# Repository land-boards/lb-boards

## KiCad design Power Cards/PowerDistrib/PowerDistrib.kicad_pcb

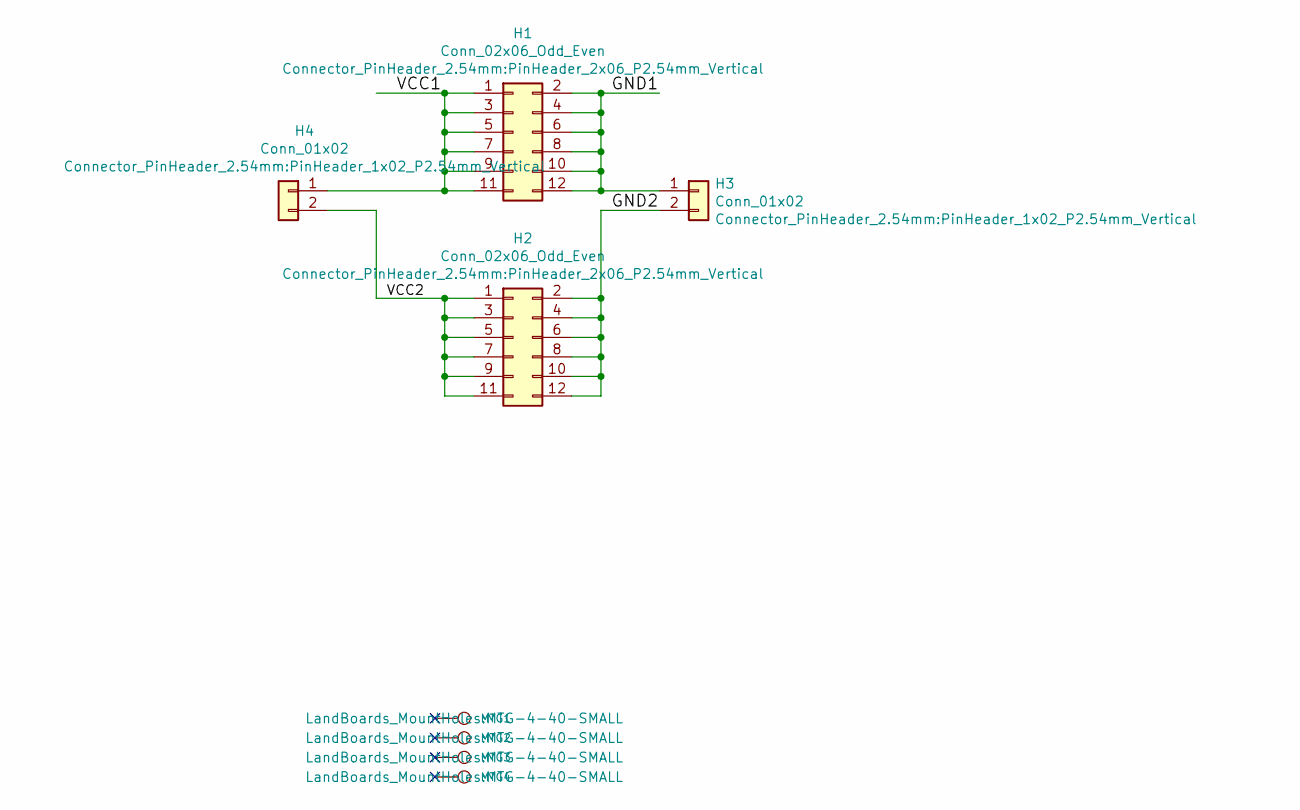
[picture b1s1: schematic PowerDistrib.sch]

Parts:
H1, H2: Conn_02x06_Odd_Even; PinHeader_2x06_P2.54mm_Vertical
H3, H4: Conn_01x02; PinHeader_1x02_P2.54mm_Vertical
MTG1, MTG2, MTG3, MTG4: CONN_1; MTG-4-40-SMALL

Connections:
/GND1: H1.2, H1.4, H1.6, H1.8, H1.10, H1.12, H3.1
/GND2: H2.2, H2.4, H2.6, H2.8, H2.10, H2.12, H3.2
/VCC1: H1.1, H1.3, H1.5, H1.7, H1.9, H1.11, H4.1
/VCC2: H2.1, H2.3, H2.5, H2.7, H2.9, H2.11, H4.2

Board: 2 copper layers, 8 parts (0 on the bottom side), 4 nets, no tracks yet.

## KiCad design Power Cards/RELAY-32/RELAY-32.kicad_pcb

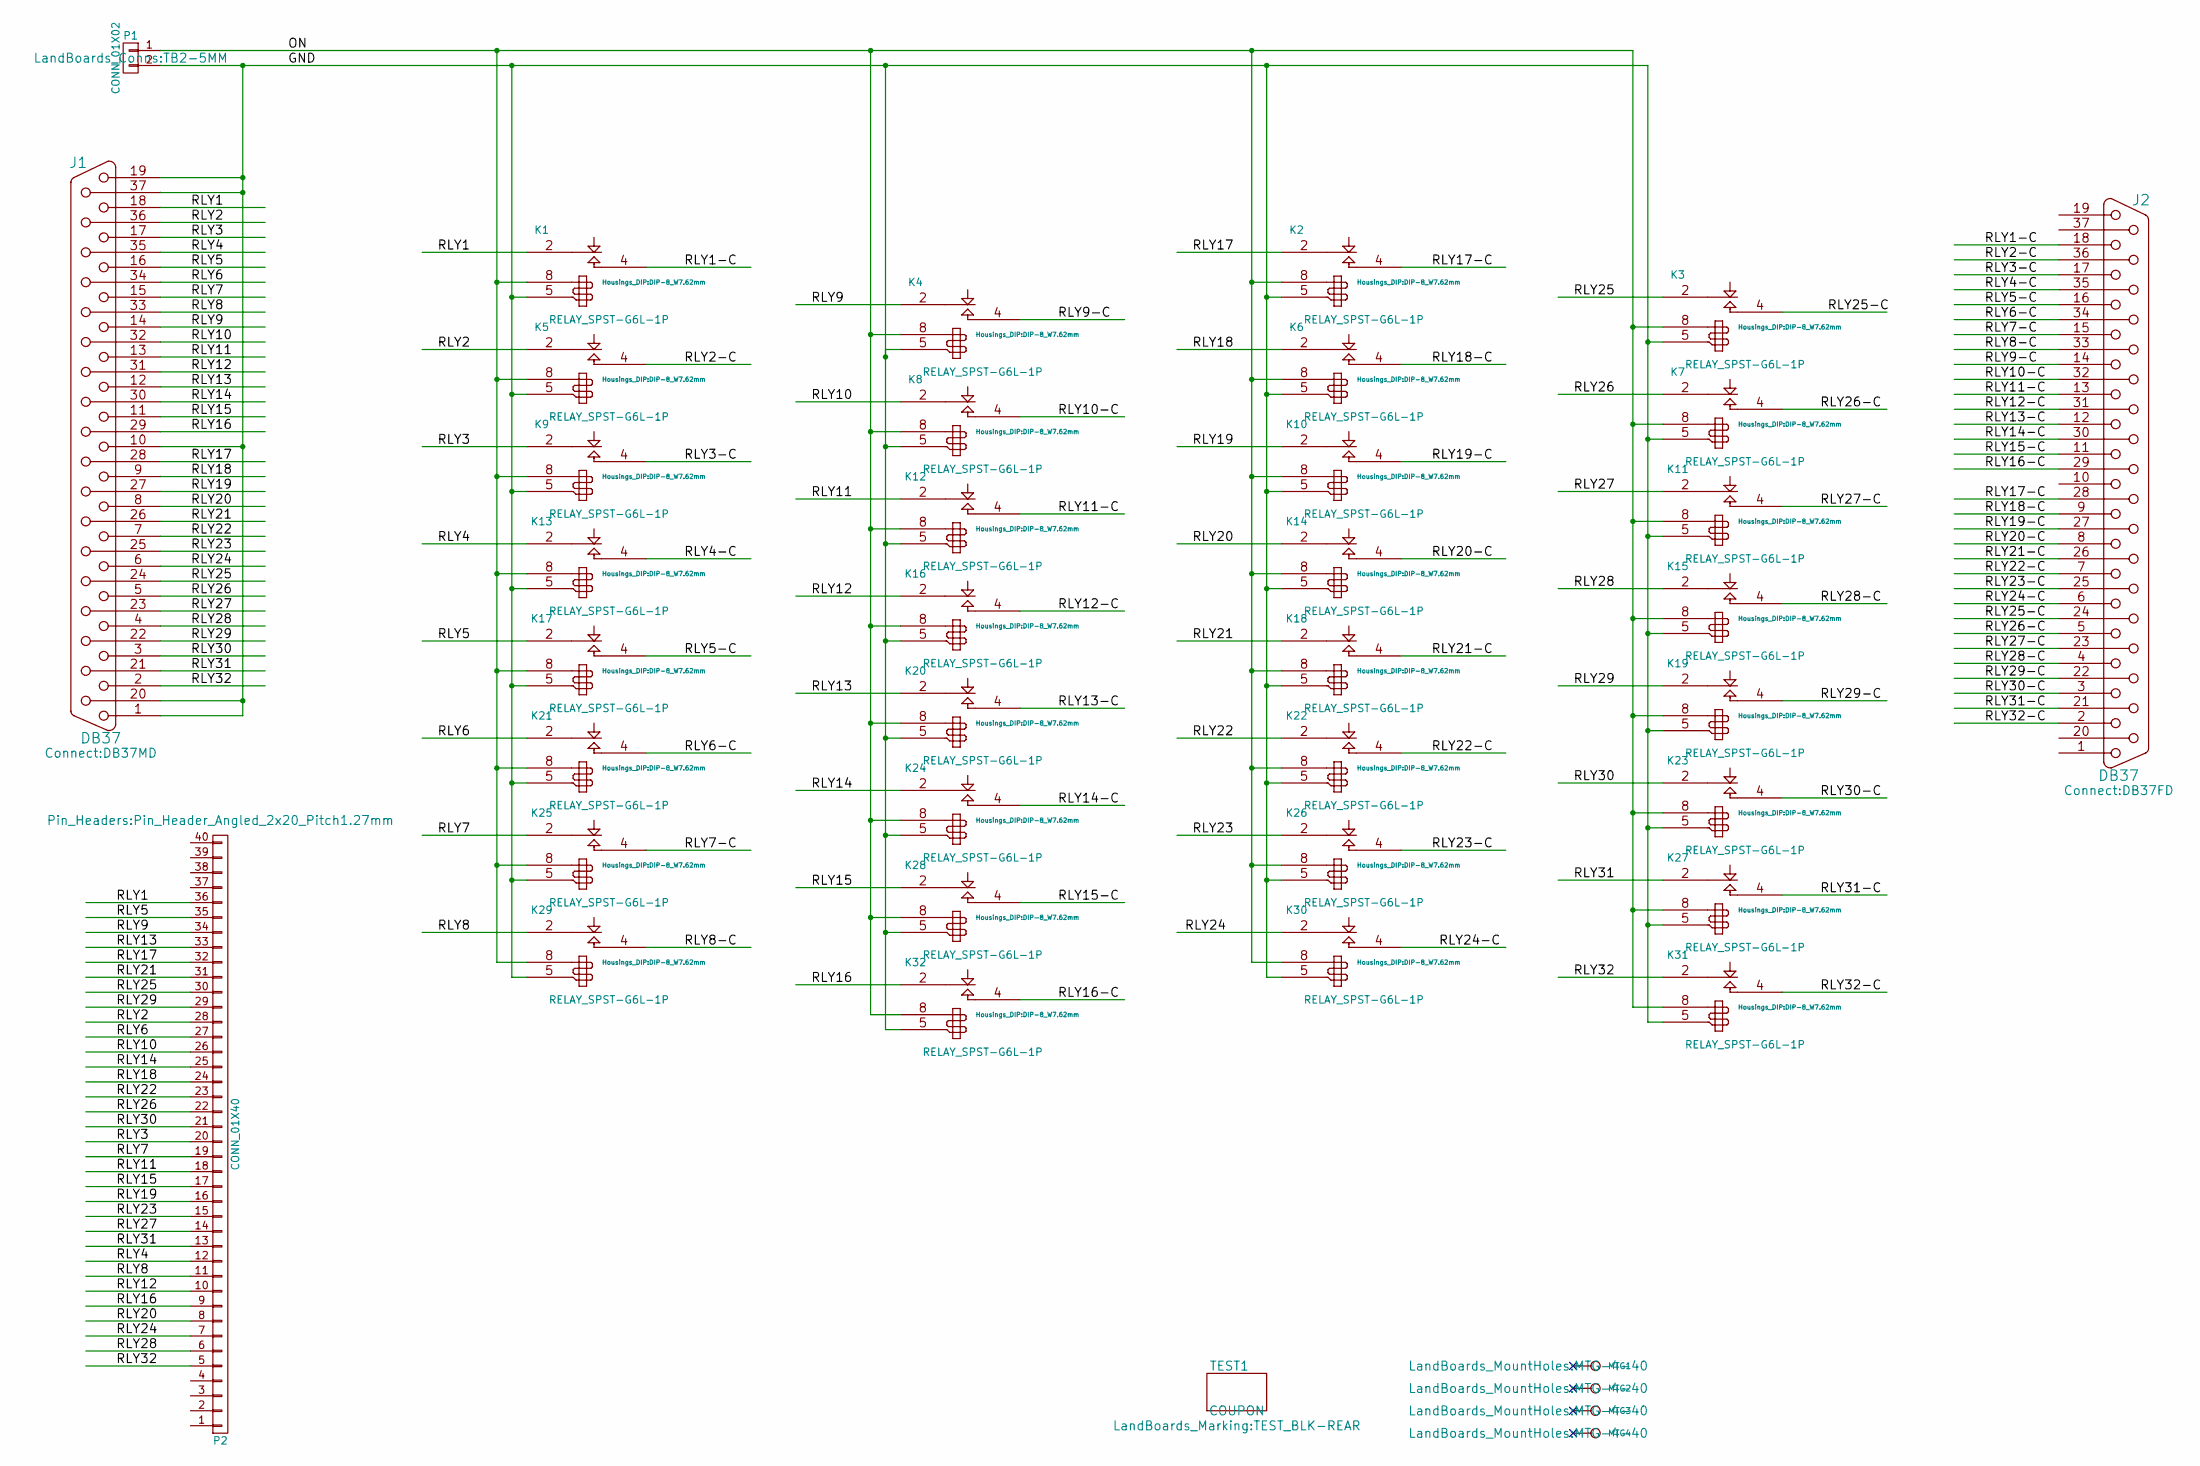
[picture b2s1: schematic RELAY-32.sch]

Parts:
J1: DB37; DB37MD
J2: DB37; DB37FD
K1, K2, K3, K4, K5, K6, K7, K8, K9, K10, K11, K12, K13, K14, K15, K16, K17, K18, K19, K20, K21, K22, K23, K24, K25, K26, K27, K28, K29, K30, K31, K32: RELAY_SPST-G6L-1P; DIP-8_W7.62mm
MTG1, MTG2, MTG3, MTG4: CONN_1; MTG-4-40
P1: CONN_01X02; TB2-5MM
P2: CONN_01X40; Pin_Header_Angled_2x20_Pitch1.27mm
TEST1: COUPON; TEST_BLK-REAR

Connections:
/GND: J1.1, J1.10, J1.19, J1.20, J1.37, K1.5, K2.5, K3.5, K4.5, K5.5, K6.5, K7.5, K8.5, K9.5, K10.5, K11.5, K12.5, K13.5, K14.5, K15.5, K16.5, K17.5, K18.5, K19.5, K20.5, K21.5, K22.5, K23.5, K24.5, K25.5, K26.5, K27.5, K28.5, K29.5, K30.5, K31.5, K32.5, P1.2
/ON: K1.8, K2.8, K3.8, K4.8, K5.8, K6.8, K7.8, K8.8, K9.8, K10.8, K11.8, K12.8, K13.8, K14.8, K15.8, K16.8, K17.8, K18.8, K19.8, K20.8, K21.8, K22.8, K23.8, K24.8, K25.8, K26.8, K27.8, K28.8, K29.8, K30.8, K31.8, K32.8, P1.1
/RLY1: J1.18, K1.2 (C1), P2.36
/RLY1-C: J2.18, K1.4 (T1)
/RLY2: J1.36, K5.2 (C1), P2.28
/RLY2-C: J2.36, K5.4 (T1)
/RLY3: J1.17, K9.2 (C1), P2.20
/RLY3-C: J2.17, K9.4 (T1)
/RLY4: J1.35, K13.2 (C1), P2.12
/RLY4-C: J2.35, K13.4 (T1)
/RLY5: J1.16, K17.2 (C1), P2.35
/RLY5-C: J2.16, K17.4 (T1)
/RLY6: J1.34, K21.2 (C1), P2.27
/RLY6-C: J2.34, K21.4 (T1)
/RLY7: J1.15, K25.2 (C1), P2.19
/RLY7-C: J2.15, K25.4 (T1)
/RLY8: J1.33, K29.2 (C1), P2.11
/RLY8-C: J2.33, K29.4 (T1)
/RLY9: J1.14, K4.2 (C1), P2.34
/RLY9-C: J2.14, K4.4 (T1)
/RLY10: J1.32, K8.2 (C1), P2.26
/RLY10-C: J2.32, K8.4 (T1)
/RLY11: J1.13, K12.2 (C1), P2.18
/RLY11-C: J2.13, K12.4 (T1)
/RLY12: J1.31, K16.2 (C1), P2.10
/RLY12-C: J2.31, K16.4 (T1)
/RLY13: J1.12, K20.2 (C1), P2.33
/RLY13-C: J2.12, K20.4 (T1)
/RLY14: J1.30, K24.2 (C1), P2.25
/RLY14-C: J2.30, K24.4 (T1)
/RLY15: J1.11, K28.2 (C1), P2.17
/RLY15-C: J2.11, K28.4 (T1)
/RLY16: J1.29, K32.2 (C1), P2.9
/RLY16-C: J2.29, K32.4 (T1)
/RLY17: J1.28, K2.2 (C1), P2.32
/RLY17-C: J2.28, K2.4 (T1)
/RLY18: J1.9, K6.2 (C1), P2.24
/RLY18-C: J2.9, K6.4 (T1)
/RLY19: J1.27, K10.2 (C1), P2.16
/RLY19-C: J2.27, K10.4 (T1)
/RLY20: J1.8, K14.2 (C1), P2.8
/RLY20-C: J2.8, K14.4 (T1)
/RLY21: J1.26, K18.2 (C1), P2.31
/RLY21-C: J2.26, K18.4 (T1)
/RLY22: J1.7, K22.2 (C1), P2.23
/RLY22-C: J2.7, K22.4 (T1)
/RLY23: J1.25, K26.2 (C1), P2.15
/RLY23-C: J2.25, K26.4 (T1)
/RLY24: J1.6, K30.2 (C1), P2.7
/RLY24-C: J2.6, K30.4 (T1)
/RLY25: J1.24, K3.2 (C1), P2.30
/RLY25-C: J2.24, K3.4 (T1)
/RLY26: J1.5, K7.2 (C1), P2.22
/RLY26-C: J2.5, K7.4 (T1)
/RLY27: J1.23, K11.2 (C1), P2.14
/RLY27-C: J2.23, K11.4 (T1)
/RLY28: J1.4, K15.2 (C1), P2.6
/RLY28-C: J2.4, K15.4 (T1)
/RLY29: J1.22, K19.2 (C1), P2.29
/RLY29-C: J2.22, K19.4 (T1)
/RLY30: J1.3, K23.2 (C1), P2.21
/RLY30-C: J2.3, K23.4 (T1)
/RLY31: J1.21, K27.2 (C1), P2.13
/RLY31-C: J2.21, K27.4 (T1)
/RLY32: J1.2, K31.2 (C1), P2.5
/RLY32-C: J2.2, K31.4 (T1)

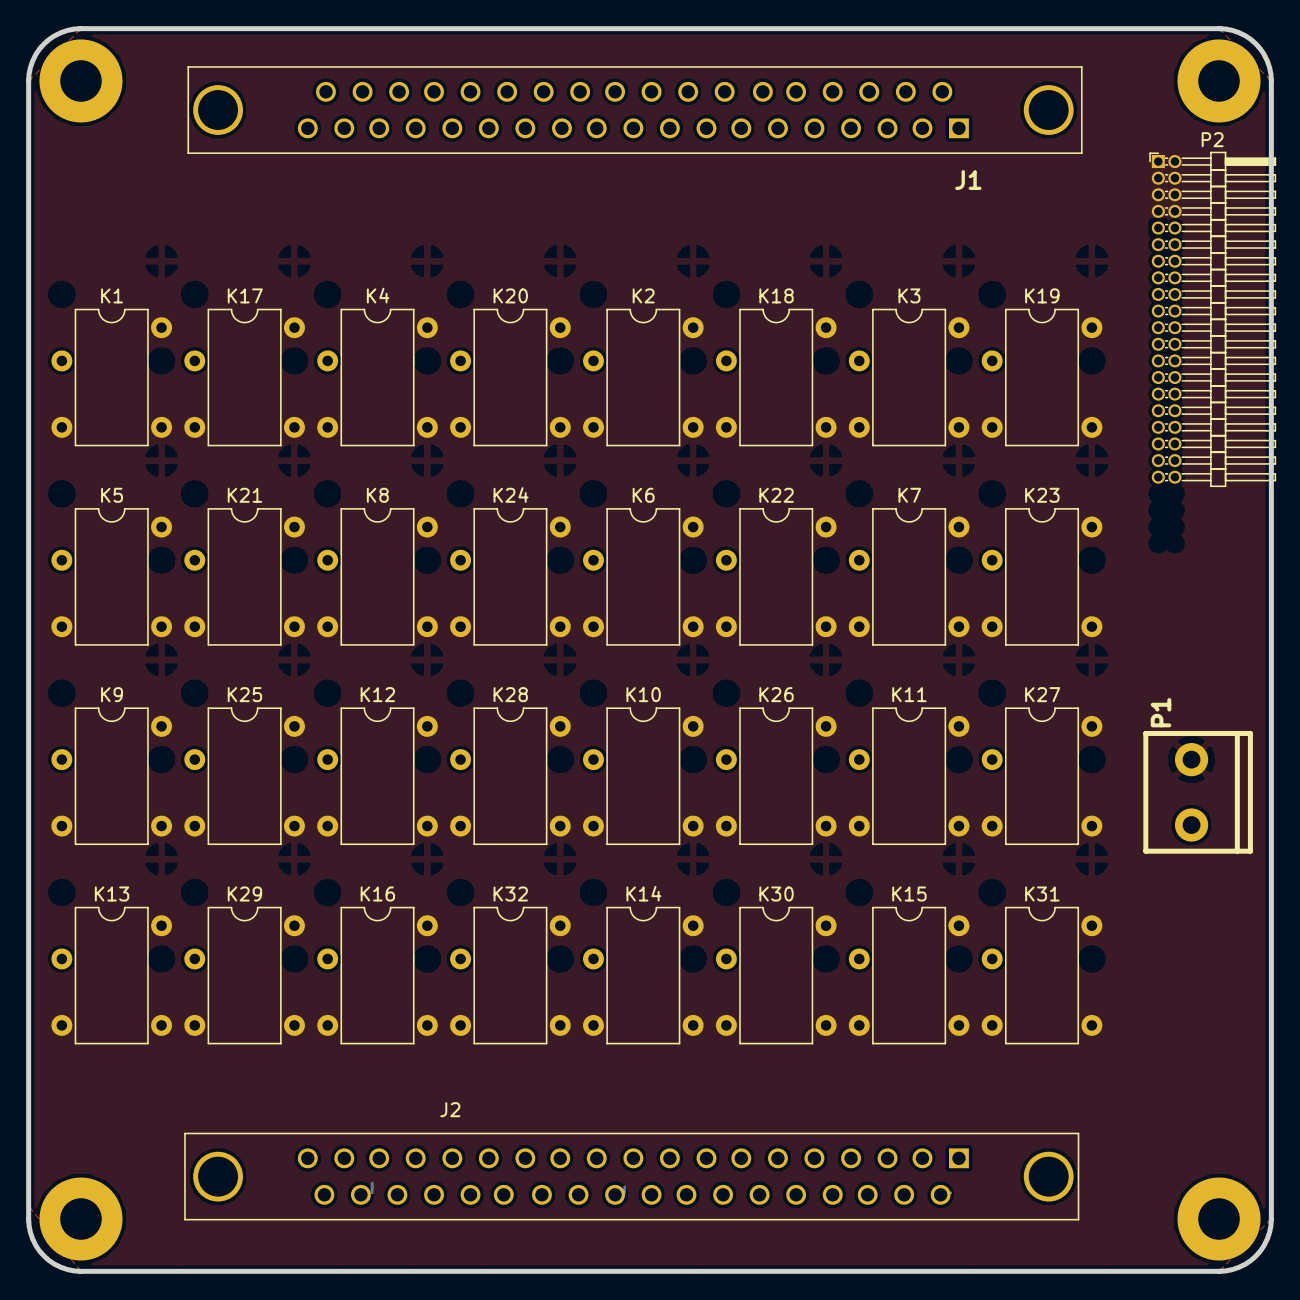
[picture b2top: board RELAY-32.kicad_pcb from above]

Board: 2 copper layers, 95.0 x 95.0 mm, 41 parts (0 on the bottom side), 66 nets.

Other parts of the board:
TEST: COUPON; TEST_BLK-REAR

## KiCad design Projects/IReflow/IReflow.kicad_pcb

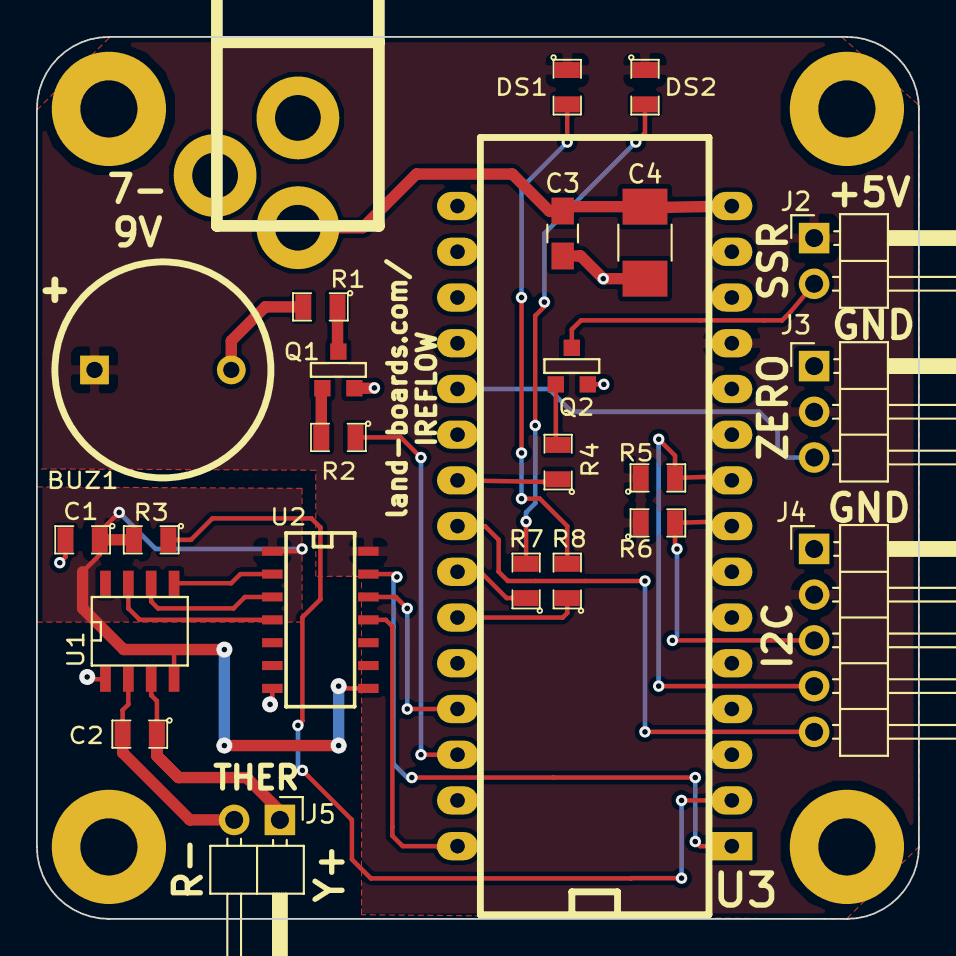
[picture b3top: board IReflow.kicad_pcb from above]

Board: 2 copper layers, 49.0 x 49.0 mm, 29 parts (0 on the bottom side), 28 nets.

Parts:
BUZ1: BUZZER; PIEZO_12MM
C1: 0.1uF; SM0805
C2: 0.01uF; SM0805
C3: 0.1uF; C_0805_HandSoldering
C4: 10uF; C_1210_HandSoldering
DS1, DS2: LED; SM0805
J1: DCJ0202; DCJ-NEW
J2, J5: CONN_2; Pin_Header_Angled_1x02_Pitch2.54mm
J3: CONN_01X03; Pin_Header_Angled_1x03_Pitch2.54mm
J4: I2CINTV2-5PIN; Pin_Header_Angled_1x05_Pitch2.54mm
MTG1, MTG2, MTG3, MTG4: CONN_1; MTG-4-40
Q1, Q2: 2N3904; SOT23EBC
R1: 100; SM0805
R2, R4, R5, R6: 10K; SM0805
R3: 10; SM0805
R7, R8: 330; SM0805
U1: MAX31855; SO8E
U2: TXS0104; SO14E
U3: arduino_mini

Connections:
+5V: BUZ1.1, DS1.1, DS2.1, J2.1, J3.2, J4.2, R5.1, R6.1, U2.14, U3.12
+9V: C3.1, C4.1, J1.1, U3.15
/CPU/+3.3V: R3.1, U3.2
/CPU/BUZZ: R2.1, U3.28
/CPU/CS: U2.12, U3.27
/CPU/DS1: R8.1, U3.25
/CPU/DS2: R7.1, U3.24
/CPU/INT: J4.5, U3.23
/CPU/MISO: U2.11, U3.30
/CPU/SCK: U2.13, U3.1
/CPU/SCL: J4.4, R5.2, U3.9
/CPU/SDA: J4.3, R6.2, U3.8
/CPU/SSR: R4.1, U3.22
/Thermocoupler Amplifier/THERMO+: C2.1, J5.1, U1.3
/Thermocoupler Amplifier/THERMO-: C2.2, J5.2, U1.2
/Thermocoupler Amplifier/V33COND: C1.1, R3.2, U1.4, U2.1, U2.8
GND: C1.2, C3.2, C4.2, J1.2, J1.3, J3.1, J4.1, Q1.1, Q2.1, U1.1, U2.7, U3.14, U3.19
unnamed: BUZ1.2, R1.2
unnamed: DS1.2, R8.2
unnamed: DS2.2, R7.2
unnamed: J2.2, Q2.3
unnamed: J3.3, U3.20
unnamed: Q1.2, R2.2
unnamed: Q1.3, R1.1
unnamed: Q2.2, R4.2
unnamed: U1.5, U2.2
unnamed: U1.6, U2.3
unnamed: U1.7, U2.4

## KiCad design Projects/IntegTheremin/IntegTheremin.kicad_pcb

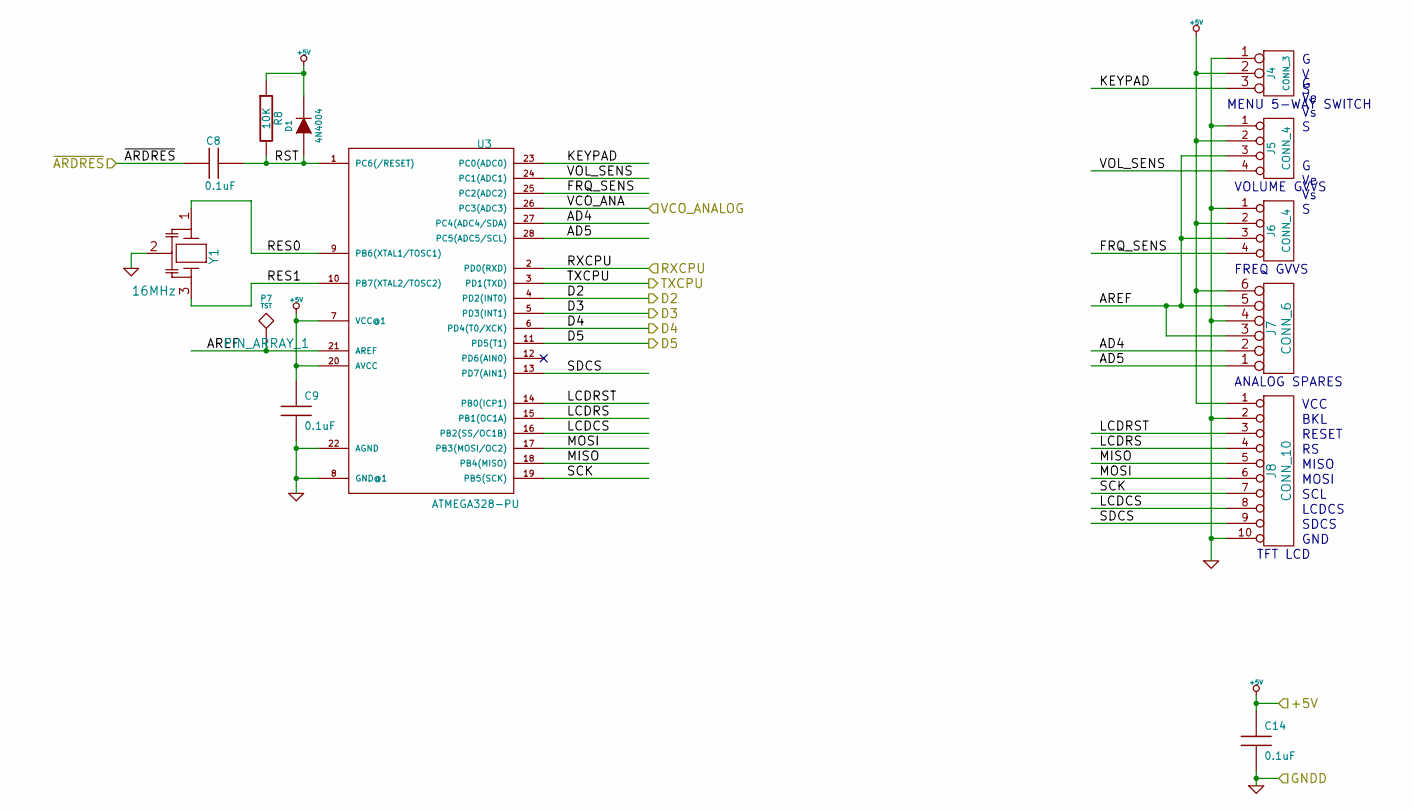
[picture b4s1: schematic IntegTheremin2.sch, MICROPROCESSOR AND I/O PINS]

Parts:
C8, C9, C14: 0.1uF; SM0805
D1: 4N4004; SOD-123
J4: CONN_3; PIN_ARRAY_3X1
J5, J6: CONN_4; PIN_ARRAY_4x1
J7: CONN_6; PIN_ARRAY-6X1
J8: CONN_10; PIN_ARRAY-10X1
P7: TST; PIN_ARRAY_1
R8: 10K; SM0805; MfgPN CRCW080510K0JNEB
U3: ATMEGA328-PU; DIP-28__300
Y1: 16MHz; RESON_3PIN; MfgPN CSTLS16M0X51-A0

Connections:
+5V: C9.1, C14.1, D1.2 (K), J4.2 (PM), J5.2, J6.2, J7.6, J8.1, R8.1, U3.7 (VCC@1), U3.20 (AVCC); also elsewhere on the board
/Digital/AD4: J7.2, U3.27 (PC4(ADC4/SDA))
/Digital/AD5: J7.1, U3.28 (PC5(ADC5/SCL))
/Digital/AREF: J5.3, J6.3, J7.3, J7.5, P7.1, U3.21 (AREF)
/Digital/D2: U3.4 (PD2(INT0)); also elsewhere on the board
/Digital/D3: U3.5 (PD3(INT1)); also elsewhere on the board
/Digital/D4: U3.6 (PD4(T0/XCK)); also elsewhere on the board
/Digital/D5: U3.11 (PD5(T1)); also elsewhere on the board
/Digital/FRQ_SENS: J6.4, U3.25 (PC2(ADC2))
/Digital/KEYPAD: J4.3, U3.23 (PC0(ADC0))
/Digital/LCDCS: J8.8, U3.16 (PB2(SS/OC1B))
/Digital/LCDRS: J8.4, U3.15 (PB1(OC1A))
/Digital/LCDRST: J8.3, U3.14 (PB0(ICP1))
/Digital/MISO: J8.5, U3.18 (PB4(MISO))
/Digital/MOSI: J8.6, U3.17 (PB3(MOSI/OC2))
/Digital/RES0: U3.9 (PB6(XTAL1/TOSC1)), Y1.1
/Digital/RES1: U3.10 (PB7(XTAL2/TOSC2)), Y1.3
/Digital/RST: C8.2, D1.1 (A), R8.2, U3.1 (PC6(/RESET))
/Digital/RXCPU: U3.2 (PD0(RXD)); also elsewhere on the board
/Digital/SCK: J8.7, U3.19 (PB5(SCK))
/Digital/SDCS: J8.9, U3.13 (PD7(AIN1))
/Digital/VCO_ANALOG: U3.26 (PC3(ADC3)); also elsewhere on the board
/Digital/VOL_SENS: J5.4, U3.24 (PC1(ADC1))
/Digital/~ARDRES: C8.1; also elsewhere on the board
/FTDI/RXFTDI: U3.3 (PD1(TXD)); also elsewhere on the board
GND: C9.2, C14.2, J4.1, J5.1, J6.1, J7.4, J8.2, J8.10, U3.8 (GND@1), U3.22 (AGND), Y1.2; also elsewhere on the board

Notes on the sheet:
G Ve Vs S
FREQ GVVS
VOLUME GVVS
ANALOG SPARES
MENU 5-WAY SWITCH
TFT LCD
SDCS
MOSI
MISO
SCL
GND
LCDCS
RESET
BKL
VCC

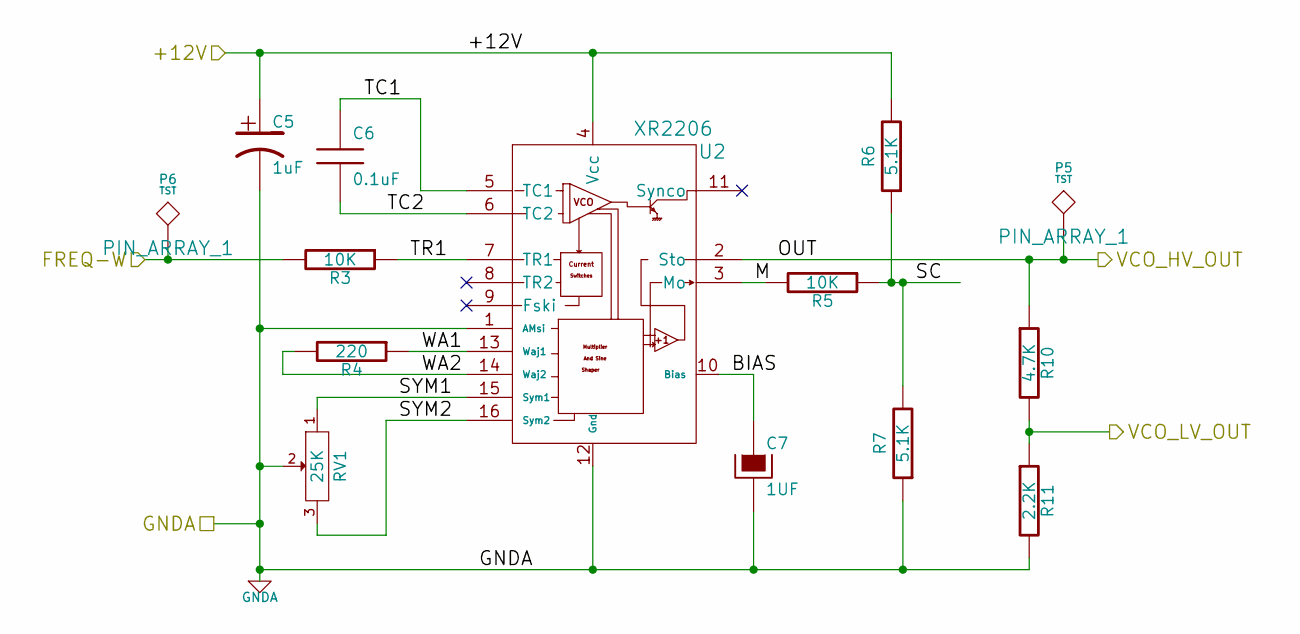
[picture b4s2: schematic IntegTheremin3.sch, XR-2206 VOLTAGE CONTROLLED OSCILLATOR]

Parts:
C5: 1uF; SM0805
C6: 0.1uF; SM0805
C7: 1UF; SM0805
P5, P6: TST; PIN_ARRAY_1
R3, R5: 10K; SM0805; MfgPN CRCW080510K0JNEB
R4: 220; SM0805; MfgPN 260-221-RC
R6, R7: 5.1K; SM0805
R10: 4.7K; SM0805
R11: 2.2K; SM0805; MfgPN 260-2.2K-RC
RV1: 25K; POT-6MM
U2: XR2206; DIP-16__300

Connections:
+12V: C5.1, R6.2, U2.4 (Vcc); also elsewhere on the board
/Digital/VCO_ANALOG: R10.2, R11.1; also elsewhere on the board
/HV Pots/AUDIO_IN: P5.1, R10.1, U2.2 (Sto); also elsewhere on the board
/HV Pots/FREQ-W: P6.1, R3.2; also elsewhere on the board
/XR-2206 VCO/BIAS: C7.1, U2.10 (Bias)
/XR-2206 VCO/M: R5.2, U2.3 (Mo)
/XR-2206 VCO/SC: R5.1, R6.1, R7.2
/XR-2206 VCO/SYM1: RV1.1, U2.15 (Sym1)
/XR-2206 VCO/SYM2: RV1.3, U2.16 (Sym2)
/XR-2206 VCO/TC1: C6.1, U2.5 (TC1)
/XR-2206 VCO/TC2: C6.2, U2.6 (TC2)
/XR-2206 VCO/TR1: R3.1, U2.7 (TR1)
/XR-2206 VCO/WA1: R4.1, U2.13 (Waj1)
/XR-2206 VCO/WA2: R4.2, U2.14 (Waj2)
GNDA: C5.2, C7.2, R7.1, R11.2, RV1.2, U2.1 (AMsi), U2.12 (Gnd); also elsewhere on the board

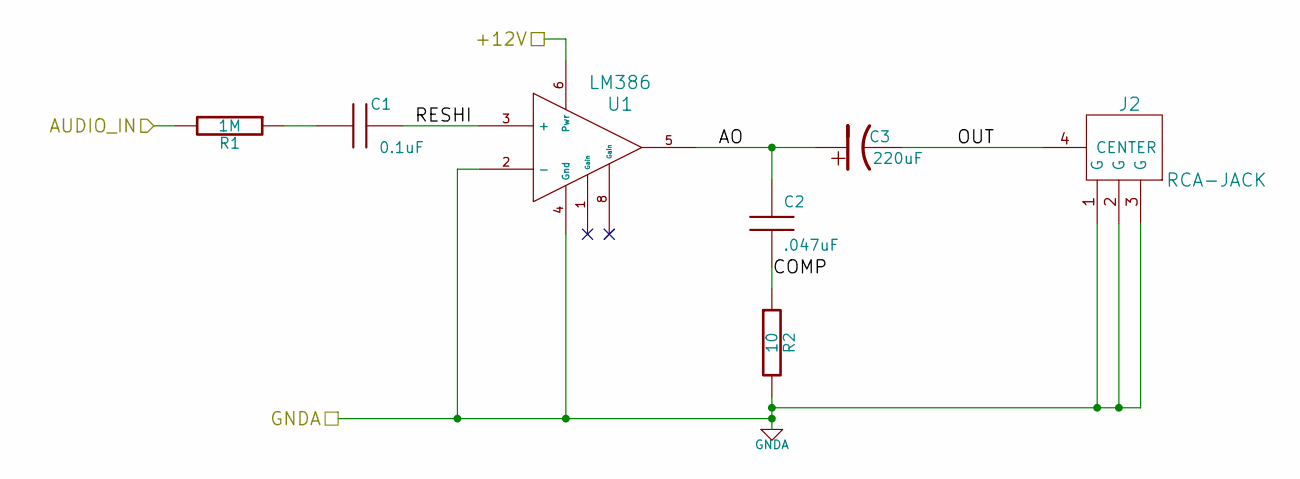
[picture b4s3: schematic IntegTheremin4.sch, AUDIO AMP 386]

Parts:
C1: 0.1uF; SM0805; MfgPN 1C10Z5U104M050B
C2: .047uF; SM0805; MfgPN VJ0805Y473JXAPW1BC
C3: 220uF; C1.25V8V; MfgPN EKMG250ELL221MHB5D
J2: RCA-JACK; RCA; MfgPN NYS354
R1: 1M; SM0805; MfgPN 260-2.2M-RC
R2: 10; SM0805; MfgPN CCF0710R0GKE36
U1: LM386; DIP-8__300; MfgPN LM386N-3/NOPB

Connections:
+12V: U1.6 (Pwr); also elsewhere on the board
/Amplifier/AO: C2.1, C3.1, U1.5
/Amplifier/COMP: C2.2, R2.1
/Amplifier/OUT: C3.2, J2.4 (CENTER)
/Amplifier/RESHI: C1.2, U1.3 (+)
/HV Pots/AUDIO-OUT: R1.2; also elsewhere on the board
GNDA: J2.1 (G), J2.2 (G), J2.3 (G), R2.2, U1.2 (-), U1.4 (Gnd); also elsewhere on the board
unnamed: C1.1, R1.1

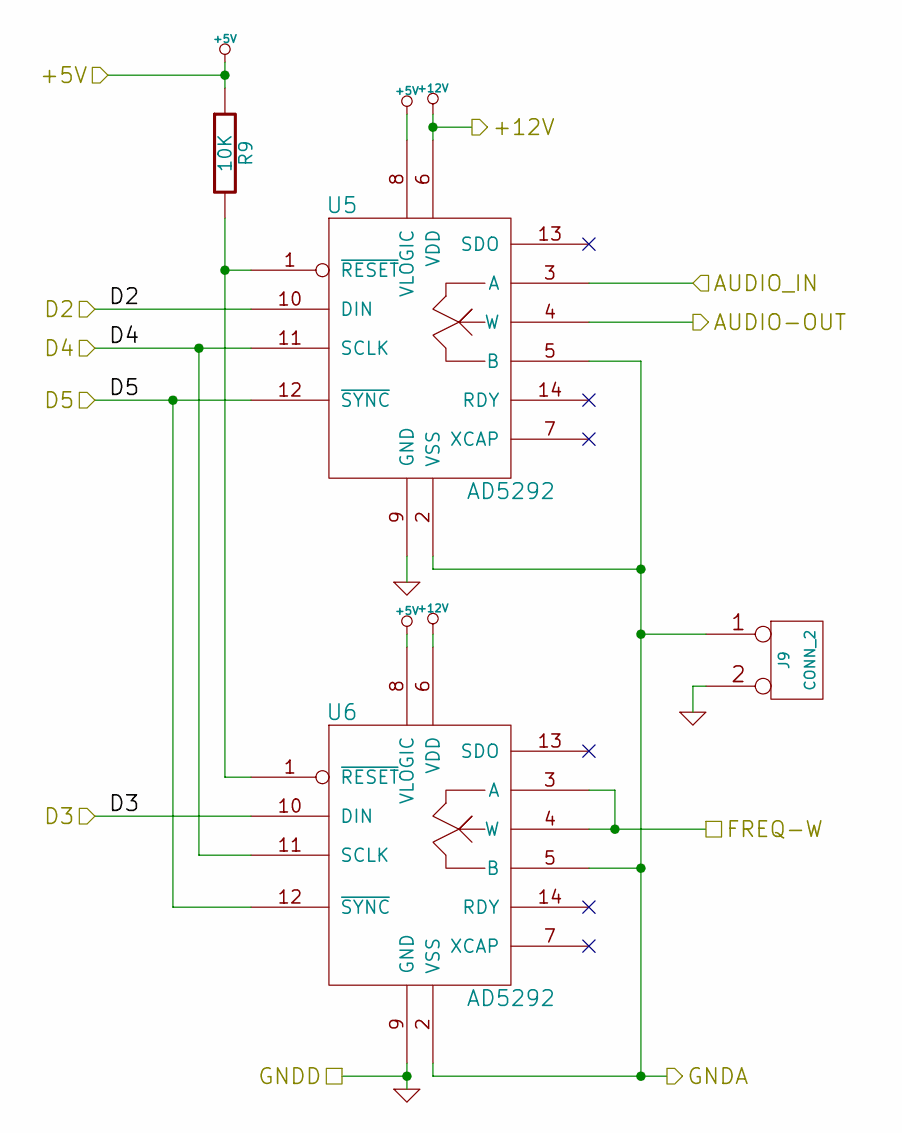
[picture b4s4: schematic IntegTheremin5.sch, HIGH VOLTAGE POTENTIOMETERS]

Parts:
J9: CONN_2; PIN_ARRAY_2X1
R9: 10K; SM0805; MfgPN CRCW080510K0JNEB
U5, U6: AD5292; tssop-14

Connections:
+5V: R9.1, U5.8 (VLOGIC), U6.8 (VLOGIC); also elsewhere on the board
+12V: U5.6 (VDD), U6.6 (VDD); also elsewhere on the board
/Digital/D2: U5.10 (DIN); also elsewhere on the board
/Digital/D3: U6.10 (DIN); also elsewhere on the board
/Digital/D4: U5.11 (SCLK), U6.11 (SCLK); also elsewhere on the board
/Digital/D5: U5.12 (~SYNC), U6.12 (~SYNC); also elsewhere on the board
/HV Pots/AUDIO-OUT: U5.4 (W); also elsewhere on the board
/HV Pots/AUDIO_IN: U5.3 (A); also elsewhere on the board
/HV Pots/FREQ-W: U6.3 (A), U6.4 (W); also elsewhere on the board
GND: J9.2 (PM), U5.9 (GND), U6.9 (GND); also elsewhere on the board
GNDA: J9.1, U5.2 (VSS), U5.5 (B), U6.2 (VSS), U6.5 (B); also elsewhere on the board
unnamed: R9.2, U5.1 (~RESET), U6.1 (~RESET)

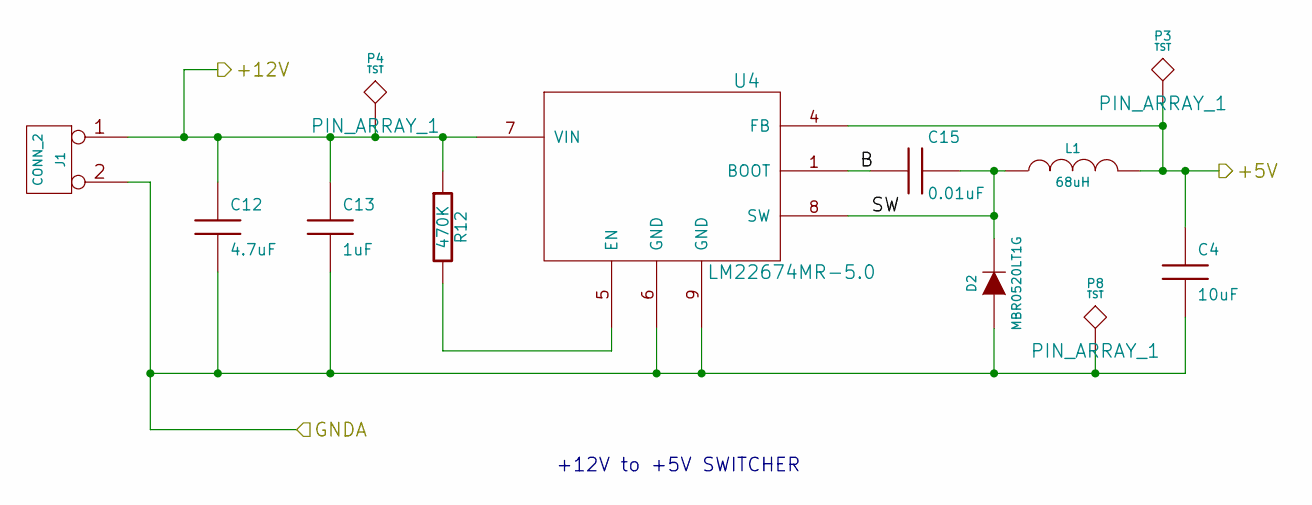
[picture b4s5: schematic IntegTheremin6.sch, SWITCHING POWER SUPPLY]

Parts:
C4: 10uF; SM1210; MfgPN C3225X5R1E106K
C12: 4.7uF; SM0805; MfgPN GRM21BR61E475MA12L
C13: 1uF; SM0805; MfgPN GRM21BR61C105MA01L
C15: 0.01uF; SM0805; MfgPN C0805C103K5RACTU
D2: MBR0520LT1G; SOD-123; MfgPN MBR0520LT1G
J1: CONN_2; TB2-5MM
L1: 68uH; IND-6MM; MfgPN SRN6045-680M
P3, P4, P8: TST; PIN_ARRAY_1
R12: 470K; SM0805
U4: LM22674MR-5.0; DDA0008B; MfgPN LM22674MR-5.0/NOPB

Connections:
+5V: C4.1, L1.2, P3.1, U4.4 (FB); also elsewhere on the board
+12V: C12.1, C13.1, J1.1, P4.1, R12.1, U4.7 (VIN); also elsewhere on the board
/Power Supply/B: C15.2, U4.1 (BOOT)
/Power Supply/SW: C15.1, D2.2 (K), L1.1, U4.8 (SW)
GNDA: C4.2, C12.2, C13.2, D2.1 (A), J1.2 (PM), P8.1, U4.6 (GND), U4.9 (GND); also elsewhere on the board
unnamed: R12.2, U4.5 (EN)

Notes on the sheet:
+12V to +5V SWITCHER

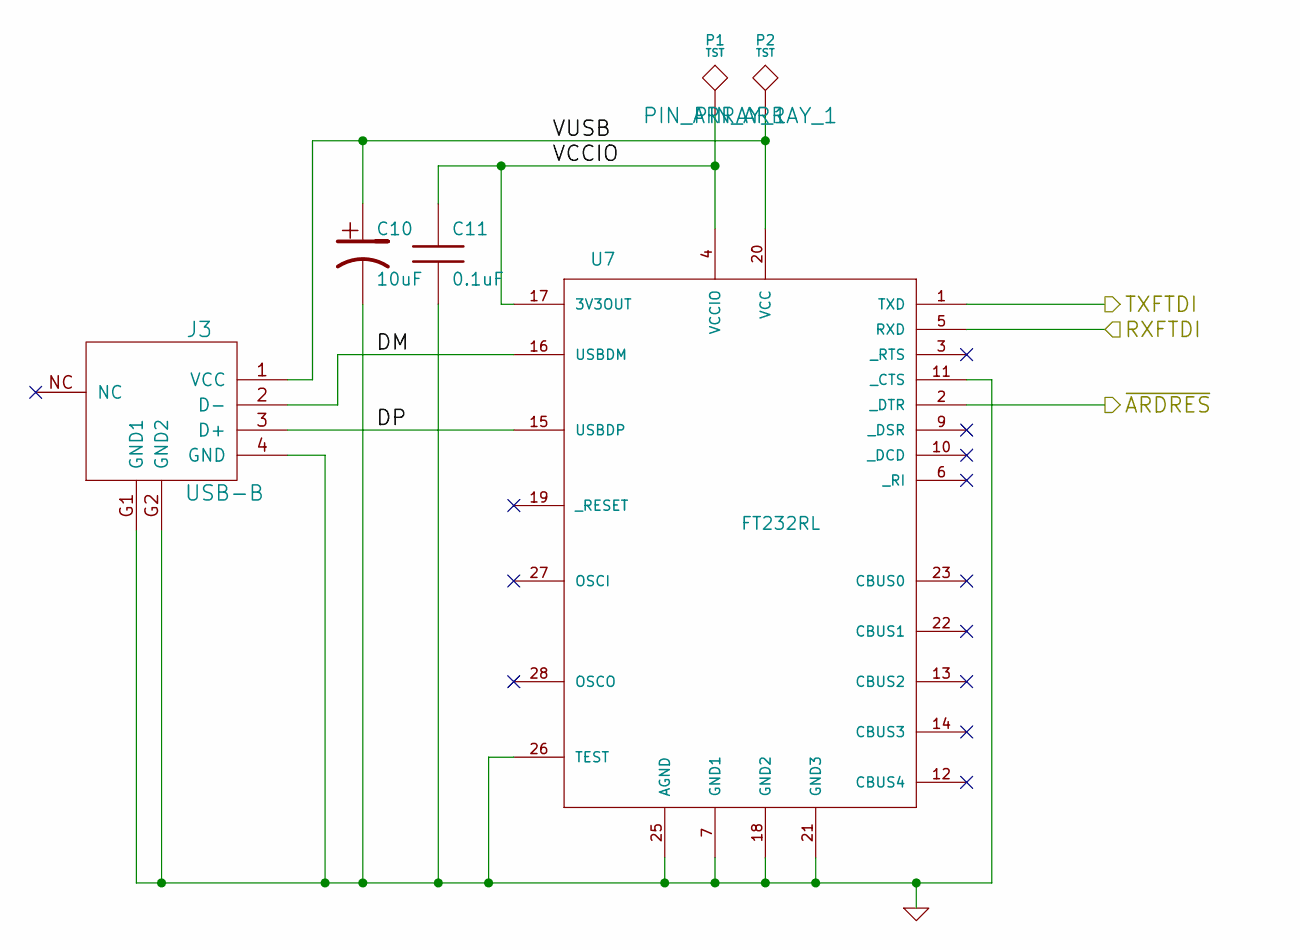
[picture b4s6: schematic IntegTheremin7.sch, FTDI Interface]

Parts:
C10: 10uF; SM1206
C11: 0.1uF; SM0805
J3: USB-B; USB-B-MINI
P1, P2: TST; PIN_ARRAY_1
U7: FT232RL; ftdichip-1-SSOP28DB

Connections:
/Digital/RXCPU: U7.1 (TXD); also elsewhere on the board
/Digital/~ARDRES: U7.2 (_DTR); also elsewhere on the board
/FTDI/DM: J3.2 (D-), U7.16 (USBDM)
/FTDI/DP: J3.3 (D+), U7.15 (USBDP)
/FTDI/RXFTDI: U7.5 (RXD); also elsewhere on the board
/FTDI/VCCIO: C11.1, P1.1, U7.4 (VCCIO), U7.17 (3V3OUT)
/FTDI/VUSB: C10.1, J3.1 (VCC), P2.1, U7.20 (VCC)
GND: C10.2, C11.2, J3.4 (GND), J3.G1 (GND1), J3.G2 (GND2), U7.7 (GND1), U7.11 (_CTS), U7.18 (GND2), U7.21 (GND3), U7.25 (AGND), U7.26 (TEST); also elsewhere on the board

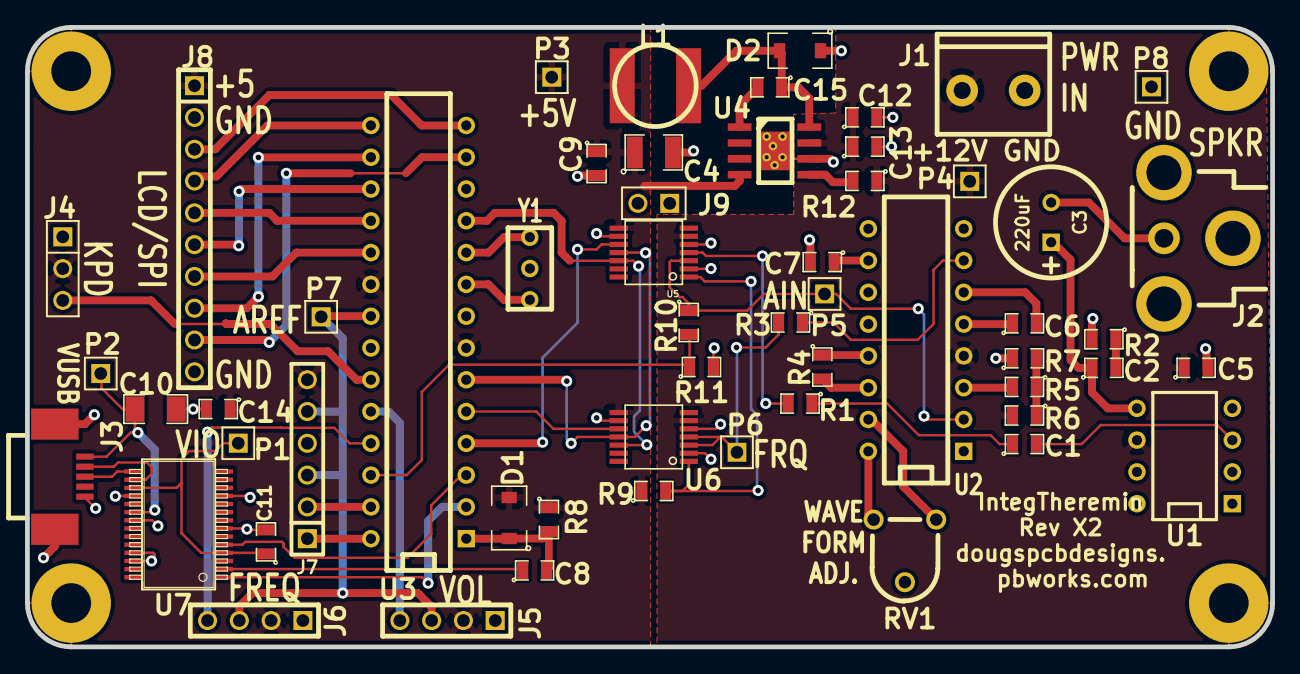
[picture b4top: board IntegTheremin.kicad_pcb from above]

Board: 2 copper layers, 99.5 x 49.5 mm, 60 parts (0 on the bottom side), 54 nets.

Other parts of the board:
MTG1, MTG2, MTG3, MTG4: CONN_1; MTG-4-40
